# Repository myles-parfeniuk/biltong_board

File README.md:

# About
Sun drying emulation controller for biltong and other dried foodstuffs,  based around STM32G070 series controller.  
Intended to be used with drying enclosures like biltong-boxes to produce sun-dried foods in non-ideal climates. 

# Table of Contents

- [About](#about)
- [PCBWay Sponsorship](#pcbway-sponsorship)
- [Hardware](#hardware)
  - [System Block Diagram](#system-block-diagram)
  - [PCB Renders](#pcb-renders)
  - [Layout](#layout)
  - [Schematics](#schematics)
- [Firmware](#firmware)
- [License](#license)
- [Contact](#contact)

# PCBWay Sponsorship
Thank you to PCBWay for reaching out to sponsor this project and provide access to their excellent service.  
PCBWay supports the DIY and open source community as well as students with sponsorships and contests frequently.   
Show them some love and consider having your next project fabricated by them: 

Order [here](https://www.pcbway.com/) today.

This was my second time using PCBWay's service, and just like last time the boards came out perfect with no defects.
While assembling the boards at home with a friend, I even had him comment the silk screen and cosmetic qualities of the board were
superior to that of domestic fabrication houses he has seen used throughout his professional career.   
To be clear, we are talking about a 0.8mm character height, with no smudging or defected labels on any part of the board, amazing!

The manufacturing and shipping time was just as fast as last time, under 2 weeks from gerber files to packages on my doorstep. 
Their customer service was also top notch. The packages were initially thought to be lost by the postage service, they offered to replace them at no cost; but, thankfully they were found the next day.  

Working with PCBWay both on this project and my previous project [here](https://github.com/myles-parfeniuk/wsen_hids_breakout) has made them my goto fabrication house. The cost to quality ratio ratio provided by their service is by far the best I have encountered. It would take a serious competitor to make me think otherwise. 

Below are some photos of the assembled main boards, along with a 3D printed case to protect the HV parts of the board, designed by [hwBirdy007](https://github.com/hwBirdy007). The quality I'm speaking of is evident when viewing, next time I want to try a different color solder mask, as PCBWay provides a wide variety of choices at no extra cost (green ,red, yellow, blue, white , and black).  
Note that the bodge wires on Y2 (low speed oscillator for RTC) are not the fault of PCBWay, I used an incorrect schematic symbol leading to an erroneous design, oops. Looks like I'll be using PCBWay again soon. This error has already been corrected in the provided KiCad files and generated gerbers.

<p align="right">(<a href="#readme-top">back to top</a>)</p>

# Hardware

Biltong board is composed of 4 separate PCBs: a main driver board, a UI/control deck board, and 2 identical temperature + humidity sensor breakout boards.   

The schematics and layout files for all boards can be found within the `hardware` directory of this repo, in the form of KiCad 7.0 projects.

The key features of each board:

Main board:
- Interfaces to drive sensor breakout boards, the control deck board,  heat lamps, and +12V PC fans.
- Stand alone power supply, no DC adapter required. 
- A magnetically isolated current sensor for linearizing the response of the triac based heat-lamp dimmer circuit. 
- A low speed oscillator and coin-cell battery interfaced to STM32's RTC for time keeping during power loss.
- A normally open safety relay to remove the lamps from circuit.
- IO expansion header, with unused GPIO for development of new features or debugging. 
- Extra mounting holes for safety cover, to prevent mishaps with high voltage side of board. 

UI/control deck board: 
- An SPI based SH1122 driven OLED display for indicating information to the user.
- 3 navigation buttons for user input.
- A buzzer to notify user attention is required. 

Sensor Breakout Board: 
- I2C based [temperature and humidity sensor](https://www.we-online.com/en/components/products/WSEN-HIDS) from Würth Elektronik for closing loop between fans and lamps.

## System Block Diagram

| SIGNAL       | PIN # | GPIO# | PERIPHERAL                       | DESCRIPTION                                                                                 |
|--------------|-------|-------|----------------------------------|---------------------------------------------------------------------------------------------|
| DISP_SCL     | 12    | PA1   | SPI1                             | SH1122 display SPI clock signal.                                                            |
| I2C1_SDA     | 32    | PA10  | I2C1                             | Temp & humidity sensor  A I2C data signal.                                                  |
| I2C2_SCL     | 33    | PA11  | I2C2                             | Temp & humidity sensor A I2C clock signal.                                                  |
| I2C2_SDA     | 34    | PA12  | I2C2                             | Temp & humidity sensor  B I2C data signal.                                                  |
| DISP_MOSI    | 13    | PA2   | SPI1                             | SH1122 display SPI data signal.                                                             |
| SW_UP        | 14    | PA3   | GPIO                             | Active low user up navigation button signal.                                                           |
| SW_ENTER     | 15    | PA4   | GPIO                             | Active low user enter/select navigation button signal.                                                 |
| SW_DOWN      | 16    | PA5   | GPIO                             | Active low user down navigation button signal.                                                         |
| FAN_B_PWM    | 17    | PA6   | TIM16_CH1 or TIM3_CH1            | Fan B PWM signal.                                                                           |
| FAN_B_TACH   | 18    | PA7   | GPIO or  TIM17_CH1 or  TIM14_CH1 | Fan B tachometer signal.                                                                    |
| I2C1_SCL     | 29    | PA9   | I2C1                             | Temp & humidity sensor B I2C clock signal.                                                  |
| FAN_A_TACH   | 19    | PB0   | GPIO or  TIM3_CH3                | Fan A tachometer signal.                                                                    |
| FAN_A_PWM    | 20    | PB1   | TIM14_CH1                        | Fan A PWM signal.                                                                           |
| UART_TX      | 22    | PB10  | USART3                           | Serial console UART TX signal for development.                                              |
| UART_RX      | 23    | PB11  | USART3                           | Serial console UART RX signal  for development.                                             |
| I_SENSE      | 21    | PB2  | ADC_IN10                         | Heat lamp current sensor output, analog signal from 0 -> vcc/2 (0A) ->vcc.                  |
| ZERO_CROSS   | 40    | PD2   | GPIO                             | Live/mains signal for sine wave zero cross detection (triac shut off point).                |
| BUZZ         | 45    | PB6   | GPIO or TIM1_CH3 or  TIM16_CH1N  | Buzzer alarm signal, frequency modulated PWM.                                               |
| DISP_CS      | 46    | PB7   | GPIO                             | SH1122 display SPI chip select signal.                                                      |
| DISP_DC      | 47    | PB8   | GPIO                             | SH1122 display data/!command signal, held low for data, high for commands.                  |
| DISP_RES     | 48    | PB9   | GPIO                             | SH1122 display reset signal.                                                                |
| TRIAC_TRIG   | 42    | PB3   | GPIO                             | Triac dimmer trigger, single pulse enables triac until instantaneous AC voltage crosses 0V. |
| HEAT_LAMP_EN | 43    | PB4   | GPIO                             | Normally open heat lamp saftey relay enable. When held high heat lamp circuit is closed.    |

<p align="right">(<a href="#readme-top">back to top</a>)</p>

## PCB Renders

### Main Board

### Control Deck Board

### Sensor Breakout Board
See [myles-parfeniuk/wsen_hids_breakout](https://github.com/myles-parfeniuk/wsen_hids_breakout).

<p align="right">(<a href="#readme-top">back to top</a>)</p>

## Layout

### Main Board

### Control Deck Board

### Sensor Breakout Board
See [myles-parfeniuk/wsen_hids_breakout](https://github.com/myles-parfeniuk/wsen_hids_breakout).

<p align="right">(<a href="#readme-top">back to top</a>)</p>

## Schematics

### Main Board

### Control Deck Board

### Sensor Breakout Board
See [myles-parfeniuk/wsen_hids_breakout](https://github.com/myles-parfeniuk/wsen_hids_breakout).

<p align="right">(<a href="#readme-top">back to top</a>)</p>

# Firmware

The firmware is currently being developed. This repo will updated as work is completed.

<p align="right">(<a href="#readme-top">back to top</a>)</p>

# License
Distributed under the GPL-3.0 License. See LICENSE.md for more information.

<p align="right">(<a href="#readme-top">back to top</a>)</p>

# Contact

Myles Parfeniuk - myles.parfenyuk@gmail.com

Project Link: [myles-parfeniuk/biltong_board](https://github.com/myles-parfeniuk/biltong_board)

<p align="right">(<a href="#readme-top">back to top</a>)</p>

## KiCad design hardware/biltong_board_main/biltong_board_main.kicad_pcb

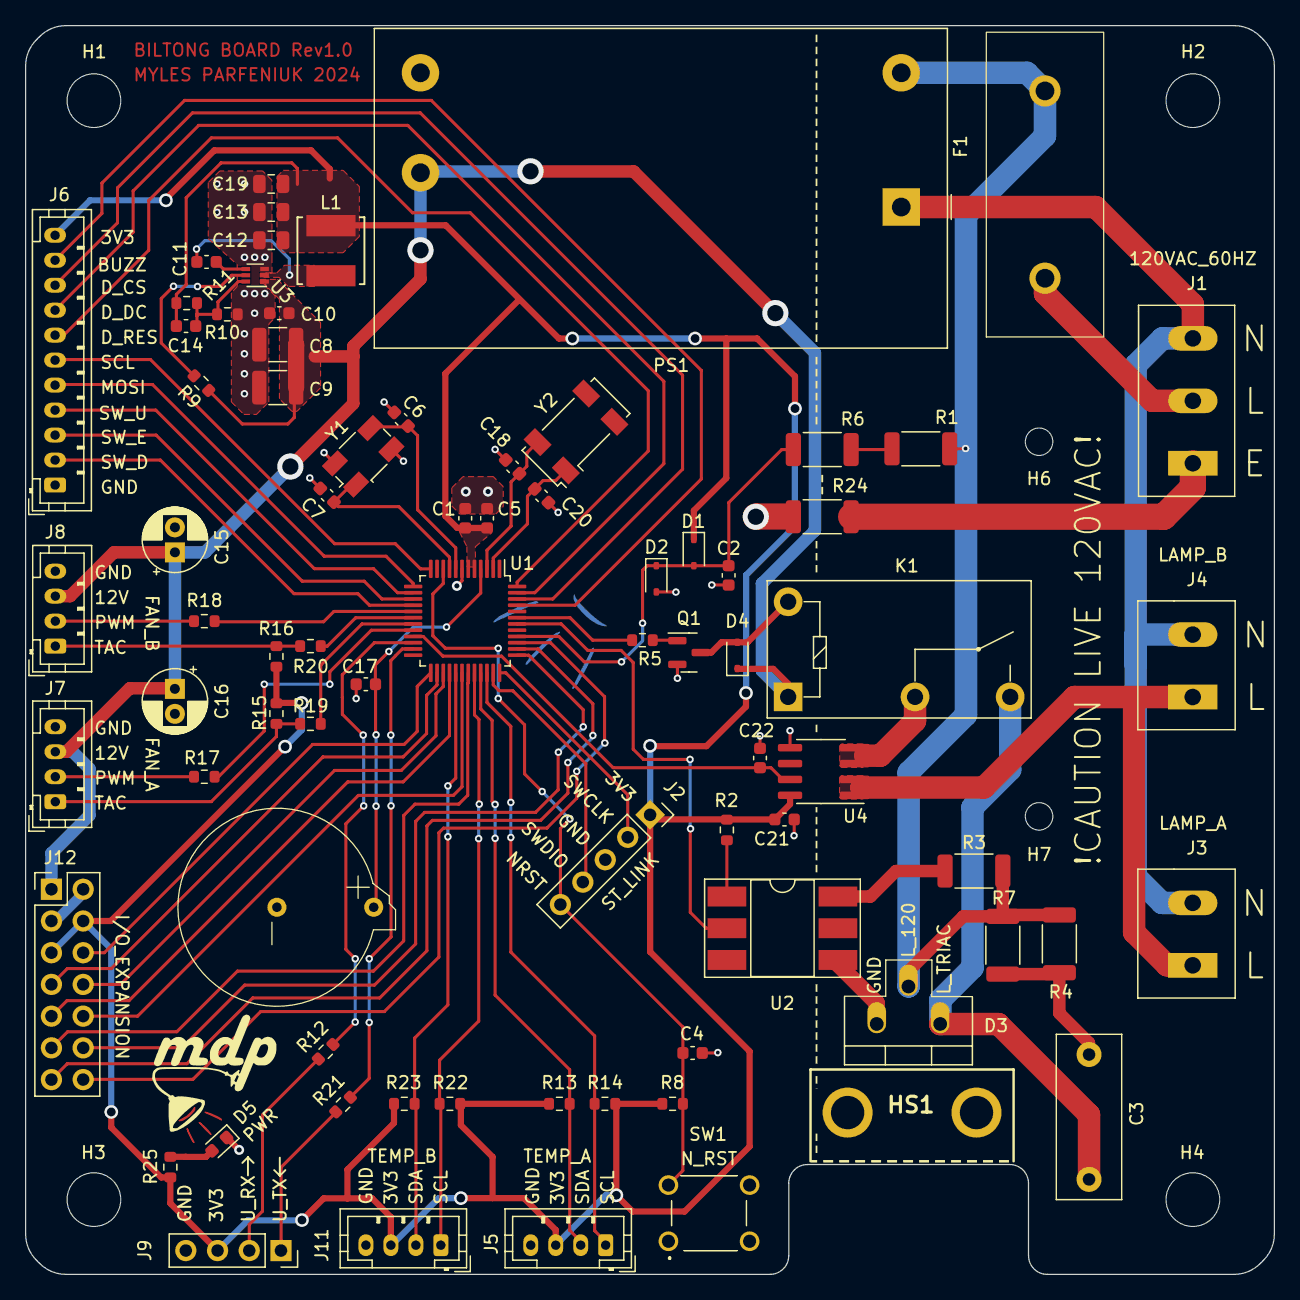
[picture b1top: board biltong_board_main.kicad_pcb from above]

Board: 2 copper layers, 100.0 x 100.0 mm, 83 parts (0 on the bottom side), 68 nets.

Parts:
BT1: BH-98-1
C1, C4, C10, C11: 100n; C_0603_1608Metric
C2: 10n; C_0603_1608Metric
C3: 10n; C_Rect_L13.0mm_W5.0mm_P10.00mm_FKS3_FKP3_MKS4
C5, C17: 1u; C_0603_1608Metric
C6, C7: 27p; C_0603_1608Metric
C8, C9: 10u; C_1210_3225Metric
C12, C13, C19: 22u; C_0805_2012Metric
C14: 47p; C_0603_1608Metric
C15, C16: 10u; CP_Radial_D5.0mm_P2.00mm
C18, C20: 15p; C_0603_1608Metric
C21: 10u; C_0603_1608Metric
C22: 1n; C_0603_1608Metric
D1, D2, D4: SD101AWS-TP; D_SOD-323
D3: Q_TRIAC_A1A2G; TO-220-3_Vertical_long_pads
D5: 150060VS7500; LED_0603_1608Metric
F1: 696106003002; fuseholder_wurth_696106003002
H1, H2, H3, H4: MountingHole M4; MountingHole_4.3mm_M4
H6, H7: MountingHole M2; MountingHole_2.2mm_M2
HS1: 581002B02500G; HSINK_581002B02500G
J1: Altech_AK300-3_P5.00mm; TerminalBlock_Altech_AK300-3_P5.00mm_w_model
J2: PinHeader_1x05_P2.54mm_Vertical; PinSocket_1x05_P2.54mm_Vertical
J3, J4: Altech_AK300-2_P5.00mm; TerminalBlock_Altech_AK300-2_P5.00mm_w_model
J5, J7, J8, J11: JST_PH_B4B-PH-K_1x04_P2.00mm_Vertical
J6: JST_PH_B11B-PH-K_1x11_P2.00mm_Vertical
J9: PinHeader_1x04_P2.54mm_Vertical; PinSocket_1x04_P2.54mm_Vertical
J12: Conn_02x07_Odd_Even; PinHeader_2x07_P2.54mm_Vertical
K1: G5Q-1A; Relay_SPST_Omron-G5Q-1A_w_model
L1: 3.3u; IND_NRS5030_TAY
PS1: IRM-10-12; Converter_ACDC_MeanWell_IRM-10-xx_THT_w_model
Q1: MMBT3904; SOT-23
R1, R6: 470K; R_2010_5025Metric
R2: 220; R_0603_1608Metric
R3: 170; R_2010_5025Metric
R4, R7: 68; R_2010_5025Metric
R5, R25: 4.7K; R_0603_1608Metric
R8, R9, R10: 10k; R_0603_1608Metric
R11: 30.9k; R_0603_1608Metric
R12, R17, R18, R19, R20, R21: 470; R_0603_1608Metric
R13, R14, R15, R16, R22, R23: 2.2K; R_0603_1608Metric
R24: 1; R_2010_5025Metric
SW1: TL1105BF250Q
U1: STM32G070CBTx; LQFP-48_7x7mm_P0.5mm
U2: MOC3023S; DIP-6_W8.89mm_SMDSocket_LongPads
U3: TPS562202SDRLR; SOT-563
U4: NSM2012-10B3R; SOIC-8_3.9x4.9mm_P1.27mm
Y1: 8MHz; Crystal_SMD_Abracon_ABM3B-4Pin_5.0x3.2mm_w_model
Y2: 32.768KHz; Crystal_SMD_Abracon_ABS25-4Pin_8.0x3.8mm_w_model

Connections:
+3V3: C1.1, C5.1, C12.1, C13.1, C14.2, C19.1, C21.1, D1.1 (K), J2.1, J5.3, J6.11, J9.3, J11.3, J12.4, J12.5, L1.2, R2.1, R8.2, R11.1, R13.2, R14.2, R15.2, R16.2, R22.2, R23.2, R25.2, U1.5 (VREF+), U1.6 (VDD), U4.8 (VCC)
+12V: C8.1, C9.1, C10.1, C15.1, C16.1, D4.1 (K), J7.3, J8.3, J12.1, K1.1, PS1.4 (+Vo), R9.2, U3.1 (VIN)
/BUZZ: J6.10, U1.45 (PB6)
/DISP_CS: J6.9, U1.46 (PB7)
/DISP_DC: J6.8, U1.47 (PB8)
/DISP_MOSI: J6.5, U1.13 (PA2)
/DISP_RES: J6.7, U1.48 (PB9)
/DISP_SCL: J6.6, U1.12 (PA1)
/FAN_A_PWM: J7.2, R17.1
/FAN_A_TACH: J7.1, R15.1, R19.1
/FAN_B_PWM: J8.2, R18.1
/FAN_B_TACH: J8.1, R16.1, R20.1
/HEAT_LAMP_EN: R5.1, U1.43 (PB4)
/I2C1_SCL: J11.2, R23.1, U1.29 (PA9/NC)
/I2C1_SDA: J11.1, R22.1, U1.32 (PA10/NC)
/I2C2_SCL: J5.2, R13.1, U1.33 (PA11/PA9)
/I2C2_SDA: J5.1, R14.1, U1.34 (PA12/PA10)
/I_SENSE: C22.1, U1.21 (PB2), U4.7 (Vout)
/L_120: D3.2 (A2), F1.2, PS1.2 (AC/L), R1.1, R3.2, R4.2, R7.2
/L_TRIAC: J3.1, J4.1, U4.1 (IP+), U4.2 (IP+)
/NRST: C4.1, J2.5, R8.1, SW1.3, U1.10 (NRST)
/N_120: J1.3, J3.2, J4.2, PS1.1 (AC/N)
/OSC32_IN: C20.1, U1.2 (PC14), Y2.1
/OSC32_OUT: C18.1, U1.3 (PC15), Y2.4
/OSC_IN: C6.1, U1.8 (PF0), Y1.3
/OSC_OUT: C7.1, U1.9 (PF1), Y1.1
/PA_8: J12.9, U1.28 (PA8)
/PA_15: J12.12, U1.37 (PA15)
/PB_13: J12.6, U1.25 (PB13)
/PB_14: J12.7, U1.26 (PB14)
/PB_15: J12.8, U1.27 (PB15)
/PC_6: J12.10, U1.30 (PC6)
/PC_7: J12.11, U1.31 (PC7)
/PD_0: J12.13, U1.38 (PD0)
/PD_1: J12.14, U1.39 (PD1)
/ST_SWCLK: J2.2, U1.36 (PA14)
/ST_SWDIO: J2.4, U1.35 (PA13)
/SW_DOWN: J6.2, U1.16 (PA5)
/SW_ENTER: J6.3, U1.15 (PA4)
/SW_UP: J6.4, U1.14 (PA3)
/TRIAC_TRIG: U1.42 (PB3), U2.2
/UART_RX: J9.1, R21.1
/UART_TX: J9.2, R12.1
/ZERO_CROSS: C2.1, D1.2 (A), D2.1 (K), R6.2, U1.40 (PD2)
Earth: HS1.1, HS1.2, J1.1, R24.1
GND: BT1.2 (-), C1.2, C2.2, C4.2, C5.2, C6.2, C7.2, C8.2, C9.2, C10.2, C12.2, C13.2, C15.2, C16.2, C17.2, C18.2, C19.2, C20.2, C21.2, C22.2, D2.2 (A), D5.1 (K), J2.3, J5.4, J6.1, J7.4, J8.4, J9.4, J11.4, J12.2, J12.3, PS1.3 (-Vo), Q1.2 (E), R10.1, R24.2, SW1.1, U1.7 (VSS), U3.3 (GND), U4.5 (GND), Y1.2, Y1.4
unnamed: C3.1, R4.1, R7.1
unnamed: C3.2, D3.1 (A1), K1.3
unnamed: D3.3 (G), U2.4
unnamed: D4.2 (A), K1.5, Q1.3 (C)
unnamed: D5.2 (A), R25.1
unnamed: F1.1, J1.2
unnamed: K1.2, U4.3 (IP-), U4.4 (IP-)
unnamed: Q1.1 (B), R5.2
unnamed: R1.2, R6.1
unnamed: R2.2, U2.1
unnamed: R3.1, U2.6
unnamed: R18.2, U1.17 (PA6)
unnamed: R20.2, U1.18 (PA7)
unnamed: R19.2, U1.19 (PB0)
unnamed: R17.2, U1.20 (PB1)
unnamed: R12.2, U1.22 (PB10)
unnamed: R21.2, U1.23 (PB11)
unnamed: C11.2, U3.4 (BST)
unnamed: R9.1, U3.5 (EN)
unnamed: C14.1, R10.2, R11.2, U3.6 (FB)
unnamed: C11.1, L1.1, U3.2 (SW)
VBAT: BT1.1 (+), C17.1, U1.4 (VBAT)

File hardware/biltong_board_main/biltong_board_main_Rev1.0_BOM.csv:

#,Reference,Qty,Value,Footprint,Digikey Product #
1,BT1,1,BH-98-1,BiltongBoardLib:BH-98-1,2057-BH-98-1-ND
2,"C1, C4, C10, C11",4,100n,Capacitor_SMD:C_0603_1608Metric,311-1341-2-ND
3,C2,1,10n,Capacitor_SMD:C_0603_1608Metric,490-4781-2-ND
4,C3,1,10n,Capacitor_THT:C_Rect_L13.0mm_W5.0mm_P10.00mm_FKS3_FKP3_MKS4,732-5724-ND
5,"C5, C17",2,1u,Capacitor_SMD:C_0603_1608Metric,1276-1946-2-ND
6,"C6, C7",2,27p,Capacitor_SMD:C_0603_1608Metric,399-C0603C270J3GAC7867TR-ND
7,"C8, C9",2,10u,Capacitor_SMD:C_1210_3225Metric,399-C1210C106M3RAC7800TR-ND
8,"C12, C13, C19",3,22u,Capacitor_SMD:C_0805_2012Metric,490-GRM21BZ70J226ME44LTR-ND
9,C14,1,47p,Capacitor_SMD:C_0603_1608Metric,1276-1037-2-ND
10,"C15, C16",2,10u,Capacitor_THT:CP_Radial_D5.0mm_P2.00mm,732-8937-1-ND
11,"C18, C20",2,15p,Capacitor_SMD:C_0603_1608Metric,311-1060-2-ND
12,C21,1,10u,Capacitor_SMD:C_0603_1608Metric,1276-1119-2-ND
13,C22,1,1n,Capacitor_SMD:C_0603_1608Metric,399-C0603C102K5RACTUTR-ND
14,"D1, D2, D4",3,SD101AWS-TP,Diode_SMD:D_SOD-323,SD101AWSTPMSTR-ND
15,D3,1,Q_TRIAC_A1A2G,Package_TO_SOT_THT:TO-220-3_Vertical,1740-1461-ND
16,D5,1,150060VS7500,LED_SMD:LED_0603_1608Metric,732-4980-2-ND
17,H5,1,581002B02500G,BiltongBoardLib:HSINK_581002B02500G,HS387-ND
18,J1,1,Altech_AK300-3_P5.00mm,BiltongBoardLib:TerminalBlock_Altech_AK300-3_P5.00mm_w_model,TC0323620000G-ND
19,J2,1,PinHeader_1x05_P2.54mm_Vertical,Connector_PinSocket_2.54mm:PinSocket_1x05_P2.54mm_Vertical,n/a
20,"J3, J4",2,Altech_AK300-2_P5.00mm,BiltongBoardLib:TerminalBlock_Altech_AK300-2_P5.00mm_w_model,TC0203620000G-ND
21,"J5, J7, J8, J11",4,JST_PH_B4B-PH-K_1x04_P2.00mm_Vertical,Connector_JST:JST_PH_B4B-PH-K_1x04_P2.00mm_Vertical,455-B4B-PH-K-ND
22,"J5, J7, J8, J11",4,JST_PH_B4B-PH-K_1x04_P2.00mm_Vertical,Connector_JST:JST_PH_B4B-PH-K_1x04_P2.00mm_Vertical,455-1164-ND
23,J6,1,JST_PH_B11B-PH-K_1x11_P2.00mm_Vertical,Connector_JST:JST_PH_B11B-PH-K_1x11_P2.00mm_Vertical,455-1713-ND
24,J6,1,JST_PH_B11B-PH-K_1x11_P2.00mm_Vertical,Connector_JST:JST_PH_B11B-PH-K_1x11_P2.00mm_Vertical,455-1157-ND
25,J9,1,PinHeader_1x04_P2.54mm_Vertical,Connector_PinSocket_2.54mm:PinSocket_1x04_P2.54mm_Vertical,n/a
26,J12,1,Conn_02x07_Odd_Even,Connector_PinHeader_2.54mm:PinHeader_2x07_P2.54mm_Vertical,n/a
27,K1,1,G5Q-1A,BiltongBoardLib:Relay_SPST_Omron-G5Q-1A_w_model,Z219-ND
28,L1,1,3.3u,BiltongBoardLib:IND_NRS5030_TAY,587-3459-2-ND
29,PS1,1,IRM-10-12,BiltongBoardLib:Converter_ACDC_MeanWell_IRM-10-xx_THT_w_model,1866-3028-ND
30,Q1,1,MMBT3904,Package_TO_SOT_SMD:SOT-23,MMBT3904
31,"R1, R6",2,470K,Resistor_SMD:R_2010_5025Metric,13-RC2010JK-07470KLTR-ND 
32,R2,1,220,Resistor_SMD:R_0603_1608Metric,A130087TR-ND
33,R3,1,170,Resistor_SMD:R_2010_5025Metric,RMCF2010JT180RTR-ND
34,"R4, R7",2,68,Resistor_SMD:R_2010_5025Metric,RMCP2010FT68R0TR-ND
35,"R5, R25",2,4.7K,Resistor_SMD:R_0603_1608Metric,RMCF0603FT4K70TR-ND
36,"R8, R9, R10",3,10k,Resistor_SMD:R_0603_1608Metric,RMCF0603JT10K0TR-ND
37,R11,1,30.9k,Resistor_SMD:R_0603_1608Metric,P30.9KHTR-ND
38,"R12, R17, R18, R19, R20, R21",6,470,Resistor_SMD:R_0603_1608Metric,311-470GRTR-ND
39,"R13, R14, R15, R16, R22, R23",6,2.2K,Resistor_SMD:R_0603_1608Metric,311-2.20KHRTR-ND
40,R24,1,1,Resistor_SMD:R_2010_5025Metric,RMCF2010ZT0R00TR-ND
41,SW1,1,N_RST,BiltongBoardLib:SW_PUSH_6mm_H5mm_4_pin,EG1834-ND
42,U1,1,STM32G070CBTx,Package_QFP:LQFP-48_7x7mm_P0.5mm,497-STM32G070CBT6-ND
43,U2,1,MOC3023S,Package_DIP:DIP-6_W8.89mm_SMDSocket_LongPads,160-1379-5-ND
44,U3,1,TPS562202SDRLR,Package_TO_SOT_SMD:SOT-563,296-TPS562202SDRLRTR-ND
45,U4,1,NSM2012-10B3R,Package_SO:SOIC-8_3.9x4.9mm_P1.27mm,5380-NSM2012-10B3R-DSPRTR-ND
46,Y1,1,8MHz,BiltongBoardLib:Crystal_SMD_Abracon_ABM3B-4Pin_5.0x3.2mm_w_model,535-9720-2-ND
47,Y2,1,32.768KHz,BiltongBoardLib:Crystal_SMD_Abracon_ABS25-4Pin_8.0x3.8mm_w_model,535-9166-2-ND
48,F1,1,Fuse Holder,BiltongBoardLib:fuseholder_wurth_696106003002,732-11374-ND
49,F1,1,Fuse Holder Cover,BiltongBoardLib:fuseholder_wurth_696106003002,732-11379-ND
50,F1,1,Fuse,BiltongBoardLib:fuseholder_wurth_696106003002,F11437-ND

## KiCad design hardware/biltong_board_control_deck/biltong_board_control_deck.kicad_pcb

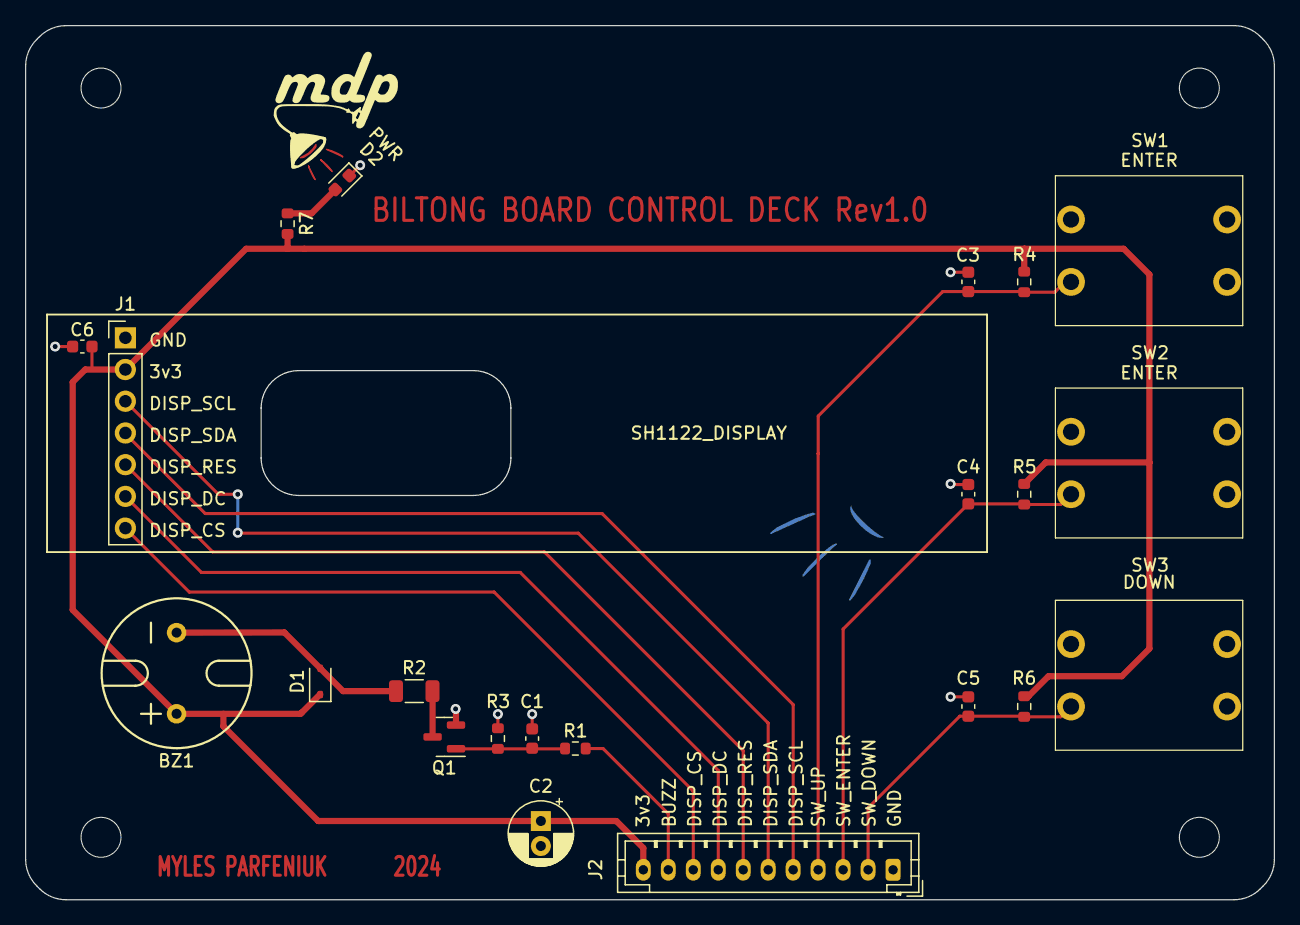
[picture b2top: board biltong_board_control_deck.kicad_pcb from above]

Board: 2 copper layers, 100.0 x 70.0 mm, 26 parts (0 on the bottom side), 15 nets.

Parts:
BZ1: GT-111P
C1: DNP; C_0603_1608Metric
C2: 10u; CP_Radial_D5.0mm_P2.00mm
C3, C4, C5: 10n; C_0603_1608Metric
C6: 1u; C_0603_1608Metric
D1: SD101AWS-TP; D_SOD-323
D2: 150060VS7500; LED_0603_1608Metric
H1, H2, H3, H4: MountingHole M3; MountingHole_3.2mm_M3
J1: PinHeader_1x07_P2.54mm_Vertical
J2: JST_PH_B11B-PH-K_1x11; JST_PH_B11B-PH-K_1x11_P2.00mm_Vertical
Q1: MMBT3904; SOT-23
R1, R7: 4.7K; R_0603_1608Metric
R2: 56; R_1206_3216Metric
R3: DNP; R_0603_1608Metric
R4, R5, R6: 10k; R_0603_1608Metric
SW1, SW2, SW3: TS14-1212-150-BK-260-SCR-D

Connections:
+3V3: BZ1.1 (-), C2.1, C6.1, D1.1 (K), J1.2, J2.11, R4.2, R5.2, R6.2, R7.2
/BUZZ: J2.10, R1.1
/DISP_CS: J1.7, J2.9
/DISP_DC: J1.6, J2.8
/DISP_MOSI: J1.4, J2.5
/DISP_RES: J1.5, J2.7
/DISP_SCL: J1.3, J2.6
/SW_DOWN: C5.1, J2.2, R6.1, SW3.3 (K)
/SW_ENTER: C4.1, J2.3, R5.1, SW2.3 (K)
/SW_UP: C3.1, J2.4, R4.1, SW1.3 (K)
GND: C1.2, C2.2, C3.2, C4.2, C5.2, C6.2, D2.1 (K), J1.1, J2.1, Q1.2 (E), R3.1, SW1.1, SW1.2, SW2.1, SW2.2, SW3.1, SW3.2
unnamed: BZ1.2 (+), D1.2 (A), R2.2
unnamed: D2.2 (A), R7.1
unnamed: C1.1, Q1.1 (B), R1.2, R3.2
unnamed: Q1.3 (C), R2.1

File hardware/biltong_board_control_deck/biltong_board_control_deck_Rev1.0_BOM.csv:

#,Reference,Qty,Value,Footprint,Digikey Product #,Alt URL
1,BZ1,1,GT-111P,BiltongBoardControlDeck:GT-111P,433-1020-ND,
2,C1,1,DNP,Capacitor_SMD:C_0603_1608Metric,n/a,
3,C2,1,10u,Capacitor_THT:CP_Radial_D5.0mm_P2.00mm,732-8937-1-ND,
4,"C3, C4, C5",3,10n,Capacitor_SMD:C_0603_1608Metric,490-4781-2-ND,
5,C6,1,1u,Capacitor_SMD:C_0603_1608Metric,1276-1946-2-ND,
6,D1,1,SD101AWS-TP,Diode_SMD:D_SOD-323,SD101AWSTPMSTR-ND,
7,D2,1,150060VS7500,LED_SMD:LED_0603_1608Metric,732-4980-2-ND,
9,J1,1,SH1122_DISP,Connector_PinHeader_2.54mm:PinHeader_1x07_P2.54mm_Vertical,n/a,SH1122 display
10,J2,1,JST_PH_B11B-PH-K_1x11,Connector_JST:JST_PH_B11B-PH-K_1x11_P2.00mm_Vertical,455-1713-ND,
11,J2,1,JST_PH_B11B-PH-K_1x11,Connector_JST:JST_PH_B11B-PH-K_1x11_P2.00mm_Vertical,455-1157-ND,
12,Q1,1,MMBT3904,Package_TO_SOT_SMD:SOT-23,MMBT3904,
13,"R1, R7",2,4.7K,Resistor_SMD:R_0603_1608Metric,RMCF0603FT4K70TR-ND,
14,R2,1,56,Resistor_SMD:R_1206_3216Metric,CRCW120656R0FKEA,
15,R3,1,DNP,Resistor_SMD:R_0603_1608Metric,n/a,
16,"R4, R5, R6",3,10k,Resistor_SMD:R_0603_1608Metric,RMCF0603JT10K0TR-ND,
,"SW1, SW2, SW3",3,TS14-1212-150-BK-260-SCR-D,BiltongBoardControlDeck:TS14-1212-150-BK-260-SCR-D,2223-TS14-1212-150-BK-260-SCR-D-ND,

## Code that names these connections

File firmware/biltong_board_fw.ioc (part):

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Mcu.Name=STM32G070CBTx
Mcu.Package=LQFP48
Mcu.UserName=STM32G070CBTx
PA1.Mode=TX_Only_Simplex_Unidirect_Master
PA1.Signal=SPI1_SCK
PA10.Mode=I2C
PA10.Signal=I2C1_SDA
PA11\ [PA9].Mode=I2C
PA11\ [PA9].Signal=I2C2_SCL
PA12\ [PA10].Mode=I2C
PA12\ [PA10].Signal=I2C2_SDA
PA2.Mode=TX_Only_Simplex_Unidirect_Master
PA2.Signal=SPI1_MOSI
PA3.GPIOParameters=GPIO_ModeDefaultEXTI
PA3.GPIO_ModeDefaultEXTI=GPIO_MODE_IT_FALLING
PA3.Signal=GPXTI3
PA4.GPIOParameters=GPIO_ModeDefaultEXTI
PA4.GPIO_ModeDefaultEXTI=GPIO_MODE_IT_FALLING
PA4.Signal=GPXTI4
PA5.GPIOParameters=GPIO_ModeDefaultEXTI
PA5.GPIO_ModeDefaultEXTI=GPIO_MODE_IT_FALLING
PA5.Signal=GPXTI5
PA6.Signal=S_TIM16_CH1
PA7.Signal=S_TIM17_CH1
PA9.Mode=I2C
PA9.Signal=I2C1_SCL
PB0.Signal=S_TIM3_CH3
PB1.Signal=S_TIM14_CH1
PB10.Mode=Asynchronous
PB10.Signal=USART3_TX
PB11.Mode=Asynchronous
PB11.Signal=USART3_RX
PB2.Mode=IN10
PB2.Signal=ADC1_IN10
PB3.GPIOParameters=GPIO_Speed,PinState
PB3.GPIO_Speed=GPIO_SPEED_FREQ_VERY_HIGH
PB3.PinState=GPIO_PIN_SET
PB3.Signal=GPIO_Output
PB4.Signal=GPIO_Output
PB6.Signal=S_TIM1_CH3
PB7.GPIOParameters=GPIO_Speed,PinState
PB7.GPIO_Speed=GPIO_SPEED_FREQ_HIGH
PB7.PinState=GPIO_PIN_SET
PB7.Signal=GPIO_Output
PB8.GPIOParameters=GPIO_Speed
PB8.GPIO_Speed=GPIO_SPEED_FREQ_HIGH
PB8.Signal=GPIO_Output
PB9.GPIOParameters=GPIO_Speed
PB9.GPIO_Speed=GPIO_SPEED_FREQ_HIGH
PB9.Signal=GPIO_Output
PC14-OSC32_IN\ (PC14).Mode=LSE-External-Oscillator
PC14-OSC32_IN\ (PC14).Signal=RCC_OSC32_IN
PC15-OSC32_OUT\ (PC15).Mode=LSE-External-Oscillator
PC15-OSC32_OUT\ (PC15).Signal=RCC_OSC32_OUT
PD0.Signal=GPIO_Output
PD2.GPIOParameters=GPIO_ModeDefaultEXTI
PD2.GPIO_ModeDefaultEXTI=GPIO_MODE_IT_RISING_FALLING
PD2.Signal=GPXTI2
PF0-OSC_IN\ (PF0).Mode=HSE-External-Oscillator
PF0-OSC_IN\ (PF0).Signal=RCC_OSC_IN
PF1-OSC_OUT\ (PF1).Mode=HSE-External-Oscillator
PF1-OSC_OUT\ (PF1).Signal=RCC_OSC_OUT
RCC.HSE_VALUE=8000000
RCC.SYSCLKFreq_VALUE=64000000
RCC.SYSCLKSource=RCC_SYSCLKSOURCE_PLLCLK
board=custom

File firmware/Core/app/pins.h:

#pragma once
// cube-mx includes
#include "gpio.h"

typedef struct biltong_gpio_t
{
        GPIO_TypeDef* port;
        uint16_t num;

        bool operator==(const biltong_gpio_t& other) const
        {
            return (this->port == other.port) && (this->num == other.num);
        }
};

// switch pins
static const constexpr biltong_gpio_t PIN_SW_UP = {GPIOA, GPIO_PIN_3};
static const constexpr biltong_gpio_t PIN_SW_ENTER = {GPIOA, GPIO_PIN_4};
static const constexpr biltong_gpio_t PIN_SW_DOWN = {GPIOA, GPIO_PIN_5};

// display pins
static const constexpr biltong_gpio_t PIN_DISP_SCL = {GPIOA, GPIO_PIN_1};
static const constexpr biltong_gpio_t PIN_DISP_MOSI = {GPIOA, GPIO_PIN_2};
static const constexpr biltong_gpio_t PIN_DISP_CS = {GPIOB, GPIO_PIN_7};
static const constexpr biltong_gpio_t PIN_DISP_DC = {GPIOB, GPIO_PIN_8};
static const constexpr biltong_gpio_t PIN_DISP_RST = {GPIOB, GPIO_PIN_9};

// uart pins
static const constexpr biltong_gpio_t PIN_UART_TX = {GPIOB, GPIO_PIN_10};
static const constexpr biltong_gpio_t PIN_UART_RX = {GPIOB, GPIO_PIN_11};

// temp/humidity sensor pins
static const constexpr biltong_gpio_t PIN_TH_B_SCL = {GPIOA, GPIO_PIN_9};
static const constexpr biltong_gpio_t PIN_TH_B_SDA = {GPIOA, GPIO_PIN_10};
static const constexpr biltong_gpio_t PIN_TH_A_SCL = {GPIOA, GPIO_PIN_11};
static const constexpr biltong_gpio_t PIN_TH_A_SDA = {GPIOA, GPIO_PIN_12};

// fan pins
static const constexpr biltong_gpio_t PIN_FAN_B_PWM = {GPIOA, GPIO_PIN_6};
static const constexpr biltong_gpio_t PIN_FAN_B_TACH = {GPIOA, GPIO_PIN_7};
static const constexpr biltong_gpio_t PIN_FAN_A_PWM = {GPIOB, GPIO_PIN_1};
static const constexpr biltong_gpio_t PIN_FAN_A_TACH = {GPIOB, GPIO_PIN_0};

// heat lamp control & feedback pins
static const constexpr biltong_gpio_t PIN_TRIAC_TRIG = {GPIOB, GPIO_PIN_3};
static const constexpr biltong_gpio_t PIN_HEAT_LAMP_EN = {GPIOB, GPIO_PIN_4};
static const constexpr biltong_gpio_t PIN_BUZZ = {GPIOB, GPIO_PIN_6};
static const constexpr biltong_gpio_t PIN_I_SENSE = {GPIOB, GPIO_PIN_12};
static const constexpr biltong_gpio_t PIN_ZERO_CROSS = {GPIOD, GPIO_PIN_2};

static const constexpr uint16_t BIT0 = (1U << 0);
static const constexpr uint16_t BIT1 = (1U << 1);
static const constexpr uint16_t BIT2 = (1U << 2);
static const constexpr uint16_t BIT3 = (1U << 3);
static const constexpr uint16_t BIT4 = (1U << 4);
static const constexpr uint16_t BIT5 = (1U << 5);
static const constexpr uint16_t BIT6 = (1U << 6);
static const constexpr uint16_t BIT7 = (1U << 7);
static const constexpr uint16_t BIT8 = (1U << 8);
static const constexpr uint16_t BIT9 = (1U << 9);
static const constexpr uint16_t BIT10 = (1U << 10);
static const constexpr uint16_t BIT11 = (1U << 11);
static const constexpr uint16_t BIT12 = (1U << 12);
static const constexpr uint16_t BIT13 = (1U << 13);
static const constexpr uint16_t BIT14 = (1U << 14);
static const constexpr uint16_t BIT15 = (1U << 15);

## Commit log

2024-10-17 pushed local repo
2024-10-17 added banner
2024-10-17 modified README.md
2024-10-18 added temp/humidity hardware submodule
2024-10-19 swapped ADC pin
2024-10-22 generated BOM, swapped 10u cap size, README.md changes
2024-10-23 Fixed HS1 ground issue, missing schematic values, README.md update
2024-10-23 corrected control deck schematic values
2024-10-23 update submodules
2024-10-23 swapped zero cross pin for EXTI_2 line, HS1 recalculation
2024-10-23 firmware stub
2024-10-23 cube code regen tidy-up script
2024-10-23 removed redundant directory
2024-10-23 tidyup script header
2024-10-23 added cortex-debugger config
2024-10-23 more .json setup for cortex-debug & intellisense
2024-10-23 typo correction
2024-10-23 eddie's branch from scratch
2024-10-23 pwm_test added
2024-10-24 fixed freertos setup issues
2024-10-26 Generated gerbers, moved cap trace, cleaned up buck fills
2024-11-09 added timers and some blinking features
2024-11-11 semaphore example
2024-11-12 boilerplate task within class setup
2024-11-25 working temperature sensor reading
2024-12-01 working temp/hum sensor with refined project structure
2024-12-01 etl successfully implemented
2024-12-01 firmware setup complete
2024-12-02 firmware template modifications
2024-12-02 Added STL models for 3D printing
2024-12-02 fixed msp init crash
2024-12-02 clang-format, SerialService, TempHumiditySensor refactoring
2024-12-02 PRINT function adjustments
2024-12-02 removed ED's build dir, further SerialService adjustments
2024-12-03 OLED driver, idle task, refactoring
2024-12-03 oled font system
2024-12-03 OLED bitmap support
2024-12-03 Observer Pattern Engine
2024-12-03 cb salvo execution guard
2024-12-04 added button template, successfully tested oled
2024-12-05 lcd screen functional
2024-12-05 updated README.md w/ PCBway sponorship (thank you!)
2024-12-06 fixed round peg square hole
2024-12-06 RTC oscillator fix, lamp connector new model & footprints
2024-12-06 build file path eddie
2024-12-06 file path build eddie
2024-12-07 Y2 correction, label corrections, new lamp & Vac conn models
2024-12-08 added script that automates interrupt files
2025-01-06 Revert "added script that automates interrupt files" Eddie pushed broken code
    This reverts commit 2c1409db9cb1cd2e05ab1e7b839e015bad4f1713.
2025-01-06 OPEEngine, UnitTest structure, better build.bat, .gitignore, reworked cmake
2025-01-12 deleted literally everything lol
2025-01-12 re-added literally everything lol
2025-01-12 added .vscode/ to gitignore
2025-01-13 working single button
2025-01-13 working button
2025-01-17 refactoring, all btns funtional, serial queue
2025-01-18 task task sz trimming
2025-01-19 integrated temp/rh sens into dev model
2025-01-19 multi platform build script
2025-01-19 fixed gitignore
2025-01-19 upgraded cubeMX ver.
2025-01-25 static task stacks, mains freq meas, heat lamp ctrl stub
2025-01-25 log levels
2025-01-26 build system overhaul
2025-01-29 integrated cube cleanup into bb_py
2025-02-01 functional heat lamp dimming
2025-02-02 button bugfix, interrupt driven UART
2025-02-02 serial svc bugfix
2025-02-04 BBEventHandler & heat_lamp_ctrl refactor
2025-02-07 refactoring, name changes
2025-02-15 heat_lamp_ctrl refactoring
